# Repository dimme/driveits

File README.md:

# Drive ITS

This is the source code and schematics for the system described in the following papers:

* D. Vlastaras, T. Abbas, D. Leston, F. Tufvesson:
Vehicle Detection through Wireless Vehicular Communication, EURASIP Journal on Wireless Communications and Networking, 2014 2014:146.
* D. Vlastaras, T. Abbas, D. Leston, F. Tufvesson:
Universal Medium Range Radar and IEEE 802.11p Modem Solution for Integrated Traffic Safety, 13th International Conference on ITS Telecommunications, Tampere, Finland, pp. 193-197, 2013-11-05.
* D. Vlastaras, D. Leston:
Improved Traffic Safety by Wireless Vehicular Communication, Lund University, Sweden, 2013-06-17.

Everything is released under the GPLv3 license. For any commercial purposes please contact dimitrios@NOSPAM@cryodev.se

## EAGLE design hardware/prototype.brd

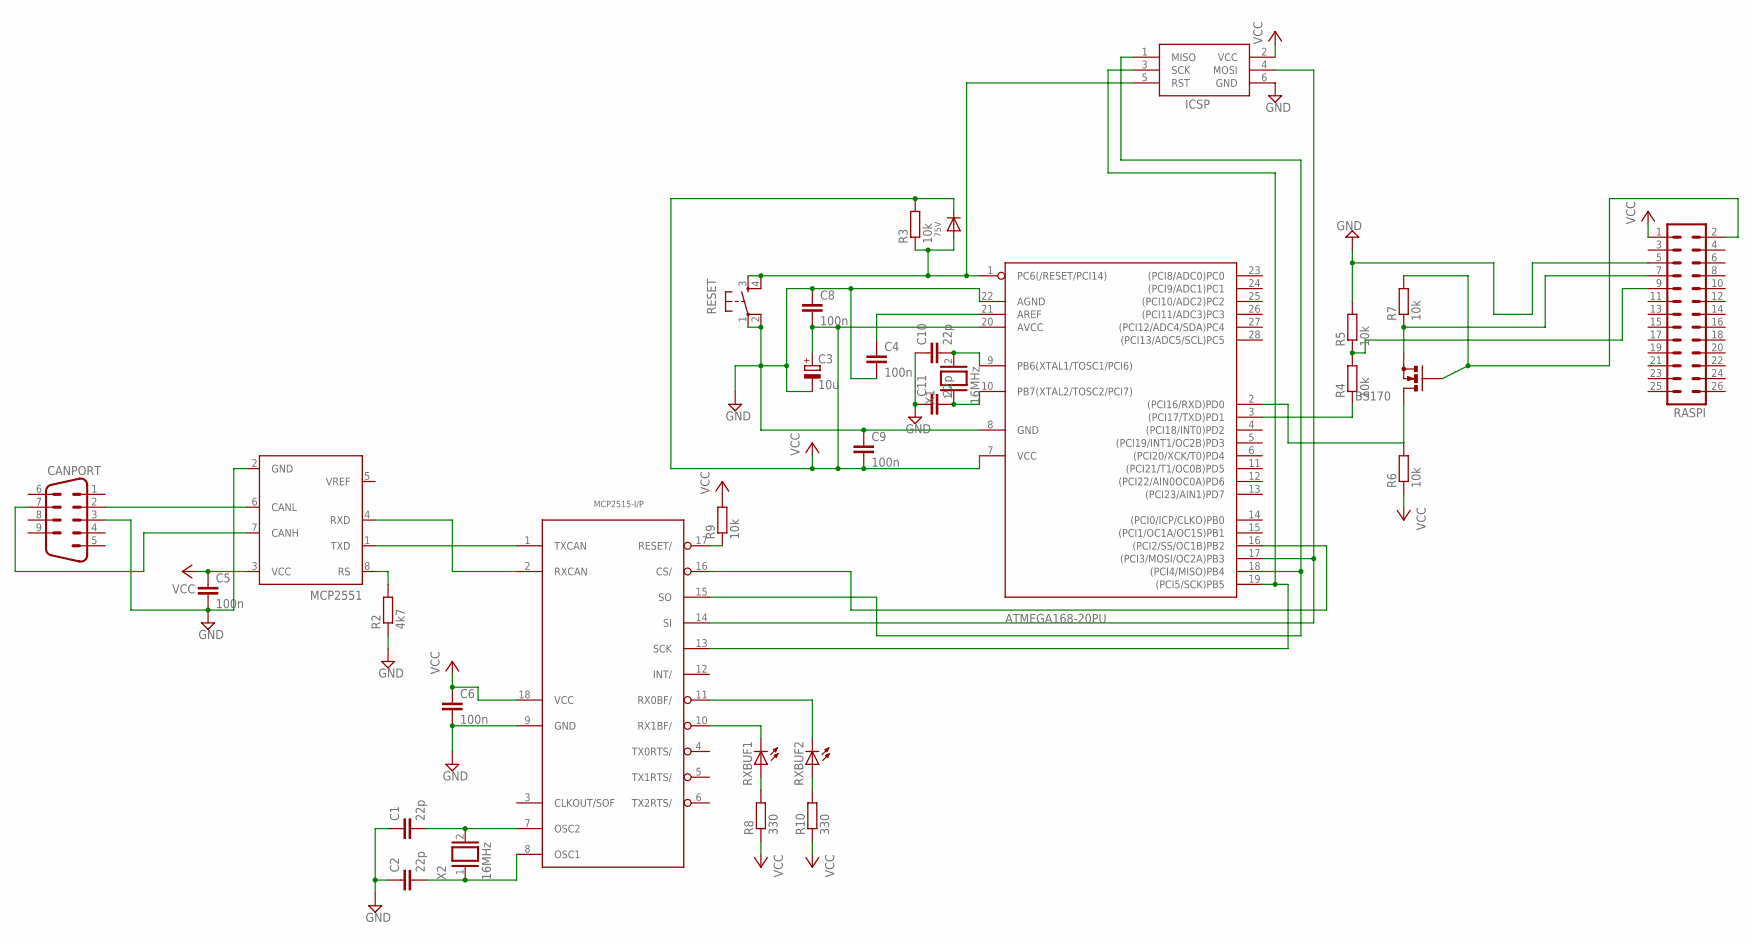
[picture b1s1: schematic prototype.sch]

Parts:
75V: DIODEDO-1N4148; DO-1N4148
ATMEGA168-20PU: ATMEGA168V-10P; DIL28-3
BS170: BS170; SOT54E
C1, C2, C10, C11: 22p; C050-025X075
C3: 10u; E2-5
C4, C5, C6, C8, C9: 100n; C050-025X075
CANPORT: M09VP
ICSP: AVRISP-6; AVRISP
MCP2515-I/P: MCP2515DIL; DIL18
MCP2551: PCA82C250; DIL08
R2: 4k7; 0204/7
R3, R4, R5, R6, R7, R9: 10k; 0204/7
R8, R10: 330; 0204/7
RASPI: MA13-2
RESET: DTS-6
RXBUF1, RXBUF2: LED5MM
X1, X2: 16MHz; QS

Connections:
GND: ATMEGA168-20PU.8 (GND), ATMEGA168-20PU.22 (AGND), C1.1, C2.1, C3.-, C4.2, C5.2, C6.2, C8.1, C9.1, C10.1, C11.1, CANPORT.3, ICSP.6 (GND), MCP2515-I/P.9 (GND), MCP2551.2 (GND), R2.1, R5.2, RASPI.5, RESET.1, RESET.2
unnamed: MCP2515-I/P.1 (TXCAN), MCP2551.1 (TXD)
unnamed: MCP2515-I/P.2 (RXCAN), MCP2551.4 (RXD)
unnamed: C1.2, MCP2515-I/P.7 (OSC2), X2.2
unnamed: C2.2, MCP2515-I/P.8 (OSC1), X2.1
unnamed: MCP2515-I/P.17 (RESET/), R9.1
unnamed: R8.2, RXBUF1.A
unnamed: R10.2, RXBUF2.A
unnamed: MCP2515-I/P.11 (RX0BF/), RXBUF2.K (C)
unnamed: MCP2515-I/P.10 (RX1BF/), RXBUF1.K (C)
unnamed: ATMEGA168-20PU.16 ((PCI2/SS/OC1B)PB2), MCP2515-I/P.16 (CS/)
unnamed: ATMEGA168-20PU.3 ((PCI17/TXD)PD1), R4.1
unnamed: ATMEGA168-20PU.19 ((PCI5/SCK)PB5), ICSP.3 (SCK), MCP2515-I/P.13 (SCK)
unnamed: ATMEGA168-20PU.9 (PB6(XTAL1/TOSC1/PCI6)), C10.2, X1.2
unnamed: ATMEGA168-20PU.10 (PB7(XTAL2/TOSC2/PCI7)), C11.2, X1.1
unnamed: MCP2551.8 (RS), R2.2
unnamed: ATMEGA168-20PU.21 (AREF), C4.1
unnamed: R4.2, R5.1, RASPI.9
unnamed: ATMEGA168-20PU.2 ((PCI16/RXD)PD0), BS170.D, R6.2
unnamed: 75V.A, ATMEGA168-20PU.1 (PC6(/RESET/PCI14)), ICSP.5 (RST), R3.1, RESET.3, RESET.4
unnamed: BS170.G, R7.2, RASPI.2
unnamed: ATMEGA168-20PU.18 ((PCI4/MISO)PB4), ICSP.1 (MISO), MCP2515-I/P.15 (SO)
unnamed: ATMEGA168-20PU.17 ((PCI3/MOSI/OC2A)PB3), ICSP.4 (MOSI), MCP2515-I/P.14 (SI)
unnamed: CANPORT.2, MCP2551.6 (CANL)
unnamed: CANPORT.7, MCP2551.7 (CANH)
unnamed: BS170.S, R7.1, RASPI.7
VCC: 75V.C, ATMEGA168-20PU.7 (VCC), ATMEGA168-20PU.20 (AVCC), C3.+, C5.1, C6.1, C8.2, C9.2, ICSP.2 (VCC), MCP2515-I/P.18 (VCC), MCP2551.3 (VCC), R3.2, R6.1, R8.1, R9.2, R10.1, RASPI.1

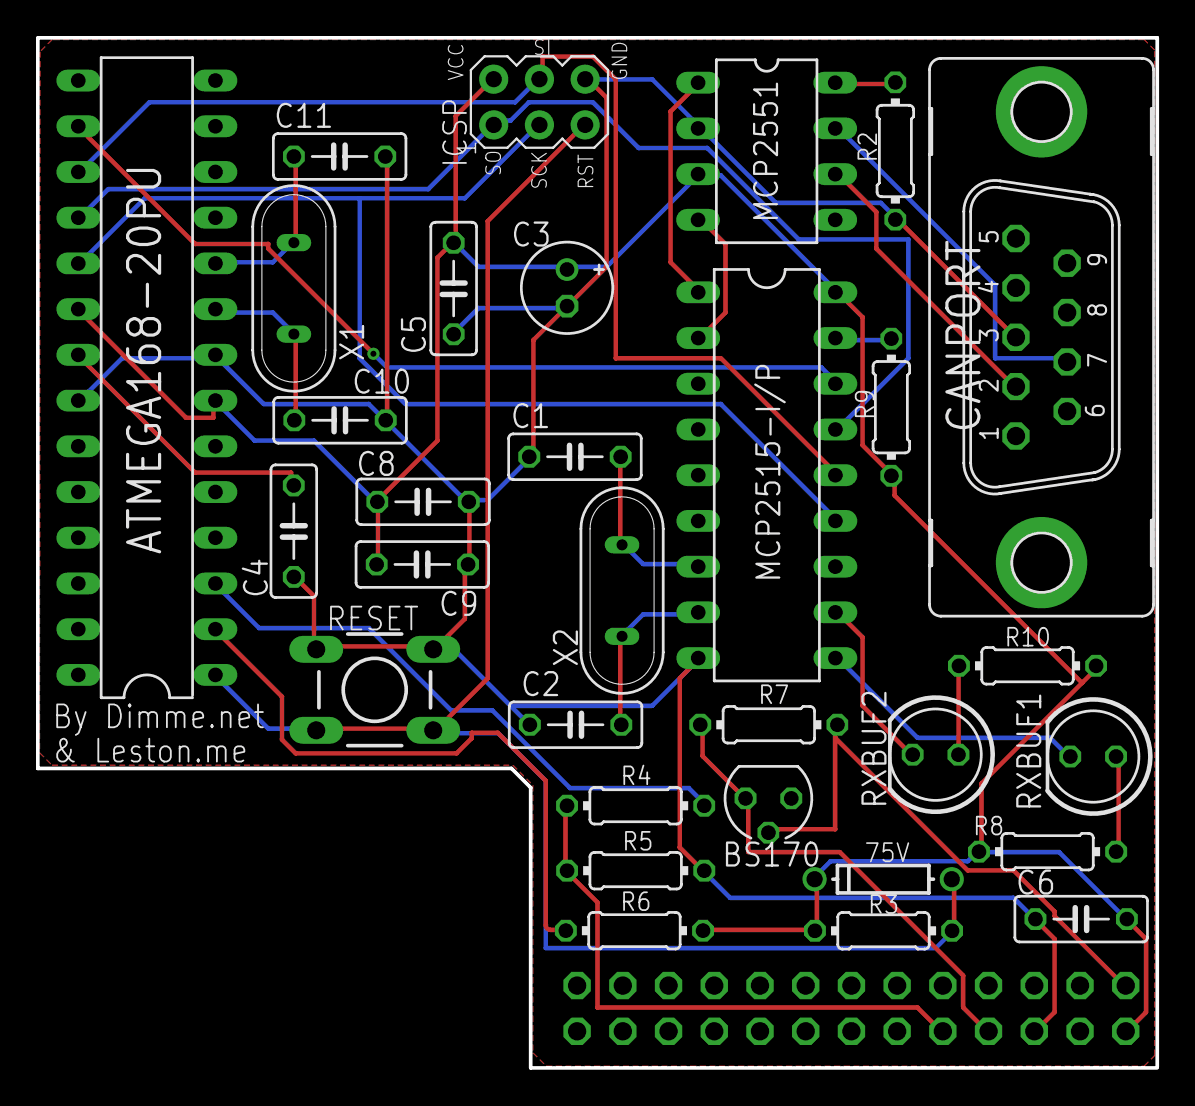
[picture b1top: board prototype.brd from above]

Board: 2 copper layers, 62.2 x 57.2 mm, 32 parts (1 on the bottom side), 27 nets.

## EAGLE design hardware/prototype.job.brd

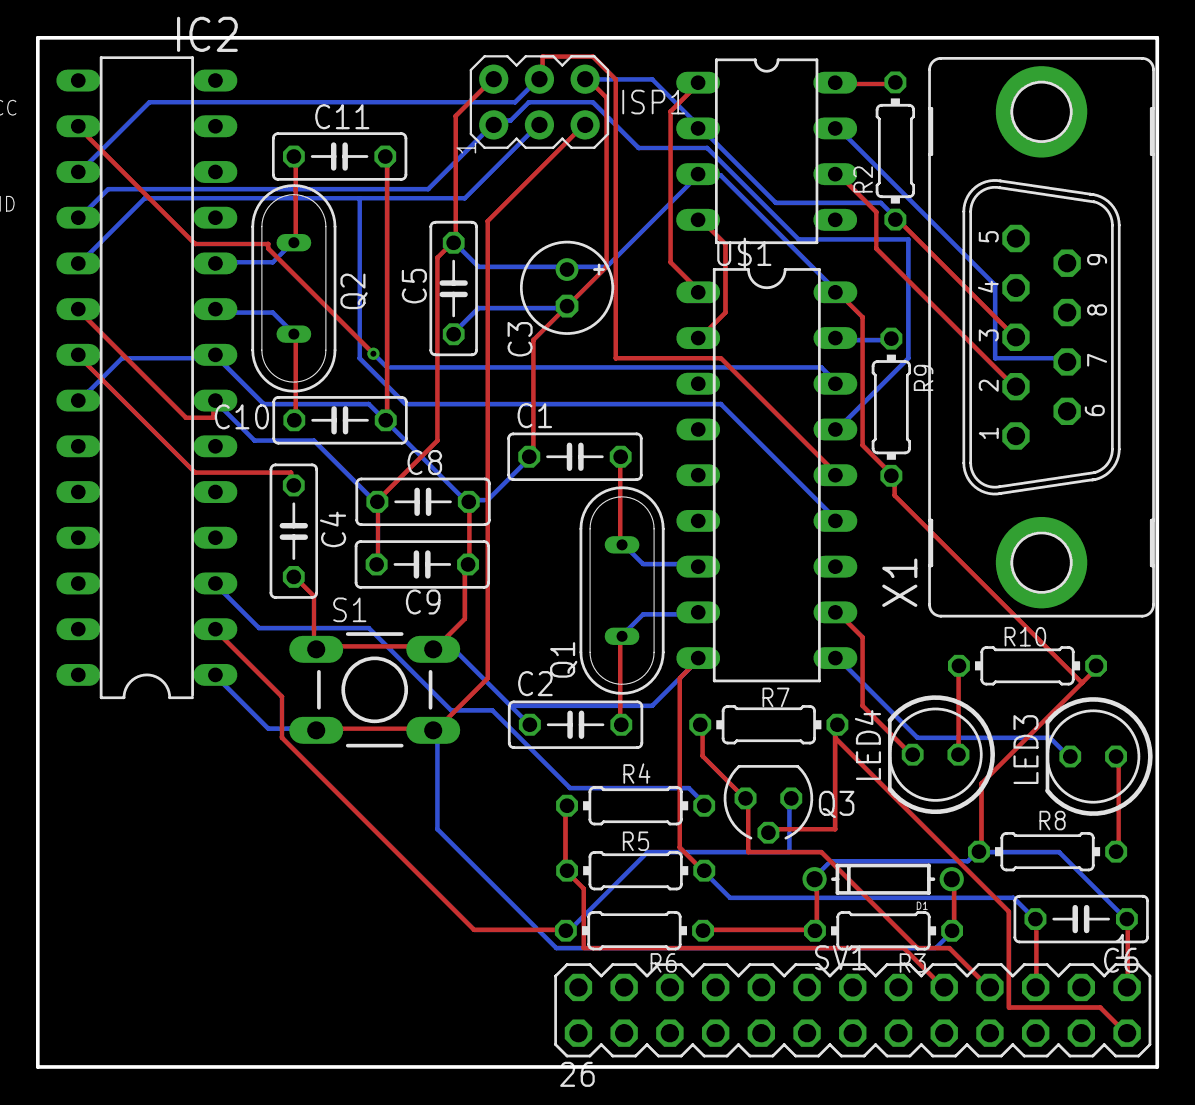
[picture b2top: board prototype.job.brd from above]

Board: 2 copper layers, 62.2 x 57.2 mm, 32 parts (0 on the bottom side), 27 nets.

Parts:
C1, C2, C4, C5, C6, C8, C9, C10, C11: C050-025X075
C3: E2-5
D1: DO-1N4148
IC1: PCA82C251; DIL08
IC2: ATMEGA328P-PU; DIL28-3
ISP1: AVRISP-6; AVRISP
LED3, LED4: LED5MM
Q1, Q2: QS
Q3: BS170; SOT54E
R2, R3, R4, R5, R6, R7, R8, R9, R10: 0204/7
S1: DTS-6
SV1: MA13-2
U$1: MCP2515DIL; DIL18
X1: M09VP

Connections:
GND: C1.1, C2.1, C3.-, C4.2, C5.2, C6.2, C8.1, C9.1, C10.1, C11.1, IC1.2, IC2.8, IC2.22, ISP1.6, R2.1, R5.2, S1.1, S1.2, SV1.5, U$1.9, X1.3
unnamed: IC1.1, U$1.1
unnamed: IC1.4, U$1.2
unnamed: C1.2, Q1.2, U$1.7
unnamed: C2.2, Q1.1, U$1.8
unnamed: R9.1, U$1.17
unnamed: LED3.A, R8.2
unnamed: LED4.A, R10.2
unnamed: LED4.K, U$1.11
unnamed: LED3.K, U$1.10
unnamed: IC2.16, U$1.16
unnamed: IC2.3, R4.1
unnamed: IC2.19, ISP1.3, U$1.13
unnamed: C10.2, IC2.9, Q2.2
unnamed: C11.2, IC2.10, Q2.1
unnamed: IC1.8, R2.2
unnamed: C4.1, IC2.21
unnamed: R4.2, R5.1, SV1.9
unnamed: IC2.2, Q3.D, R6.2
unnamed: D1.A, IC2.1, ISP1.5, R3.1, S1.3, S1.4
unnamed: Q3.G, R7.2, SV1.2
unnamed: IC2.18, ISP1.1, U$1.15
unnamed: IC2.17, ISP1.4, U$1.14
unnamed: IC1.6, X1.2
unnamed: IC1.7, X1.7
unnamed: Q3.S, R7.1, SV1.7
VCC: C3.+, C5.1, C6.1, C8.2, C9.2, D1.C, IC1.3, IC2.7, IC2.20, ISP1.2, R3.2, R6.1, R8.1, R9.2, R10.1, SV1.1, U$1.18

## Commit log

2014-12-01 first ocmmit
2014-12-01 Version of the hardware as found on the thesis
2014-12-01 Smaller PCB, also the placement of the RASPI port has been corrected and the Serial port error
2014-12-01 Added gerbers for DirtyPCBs and OSHpark.
2014-12-01 Added some images
2014-12-01 Cleanup
2014-12-03 Added software
2014-12-03 .DS_Store banished!
2014-12-04 Added GPLv3 license
2019-04-11 Hardware is not available for purchase any more
